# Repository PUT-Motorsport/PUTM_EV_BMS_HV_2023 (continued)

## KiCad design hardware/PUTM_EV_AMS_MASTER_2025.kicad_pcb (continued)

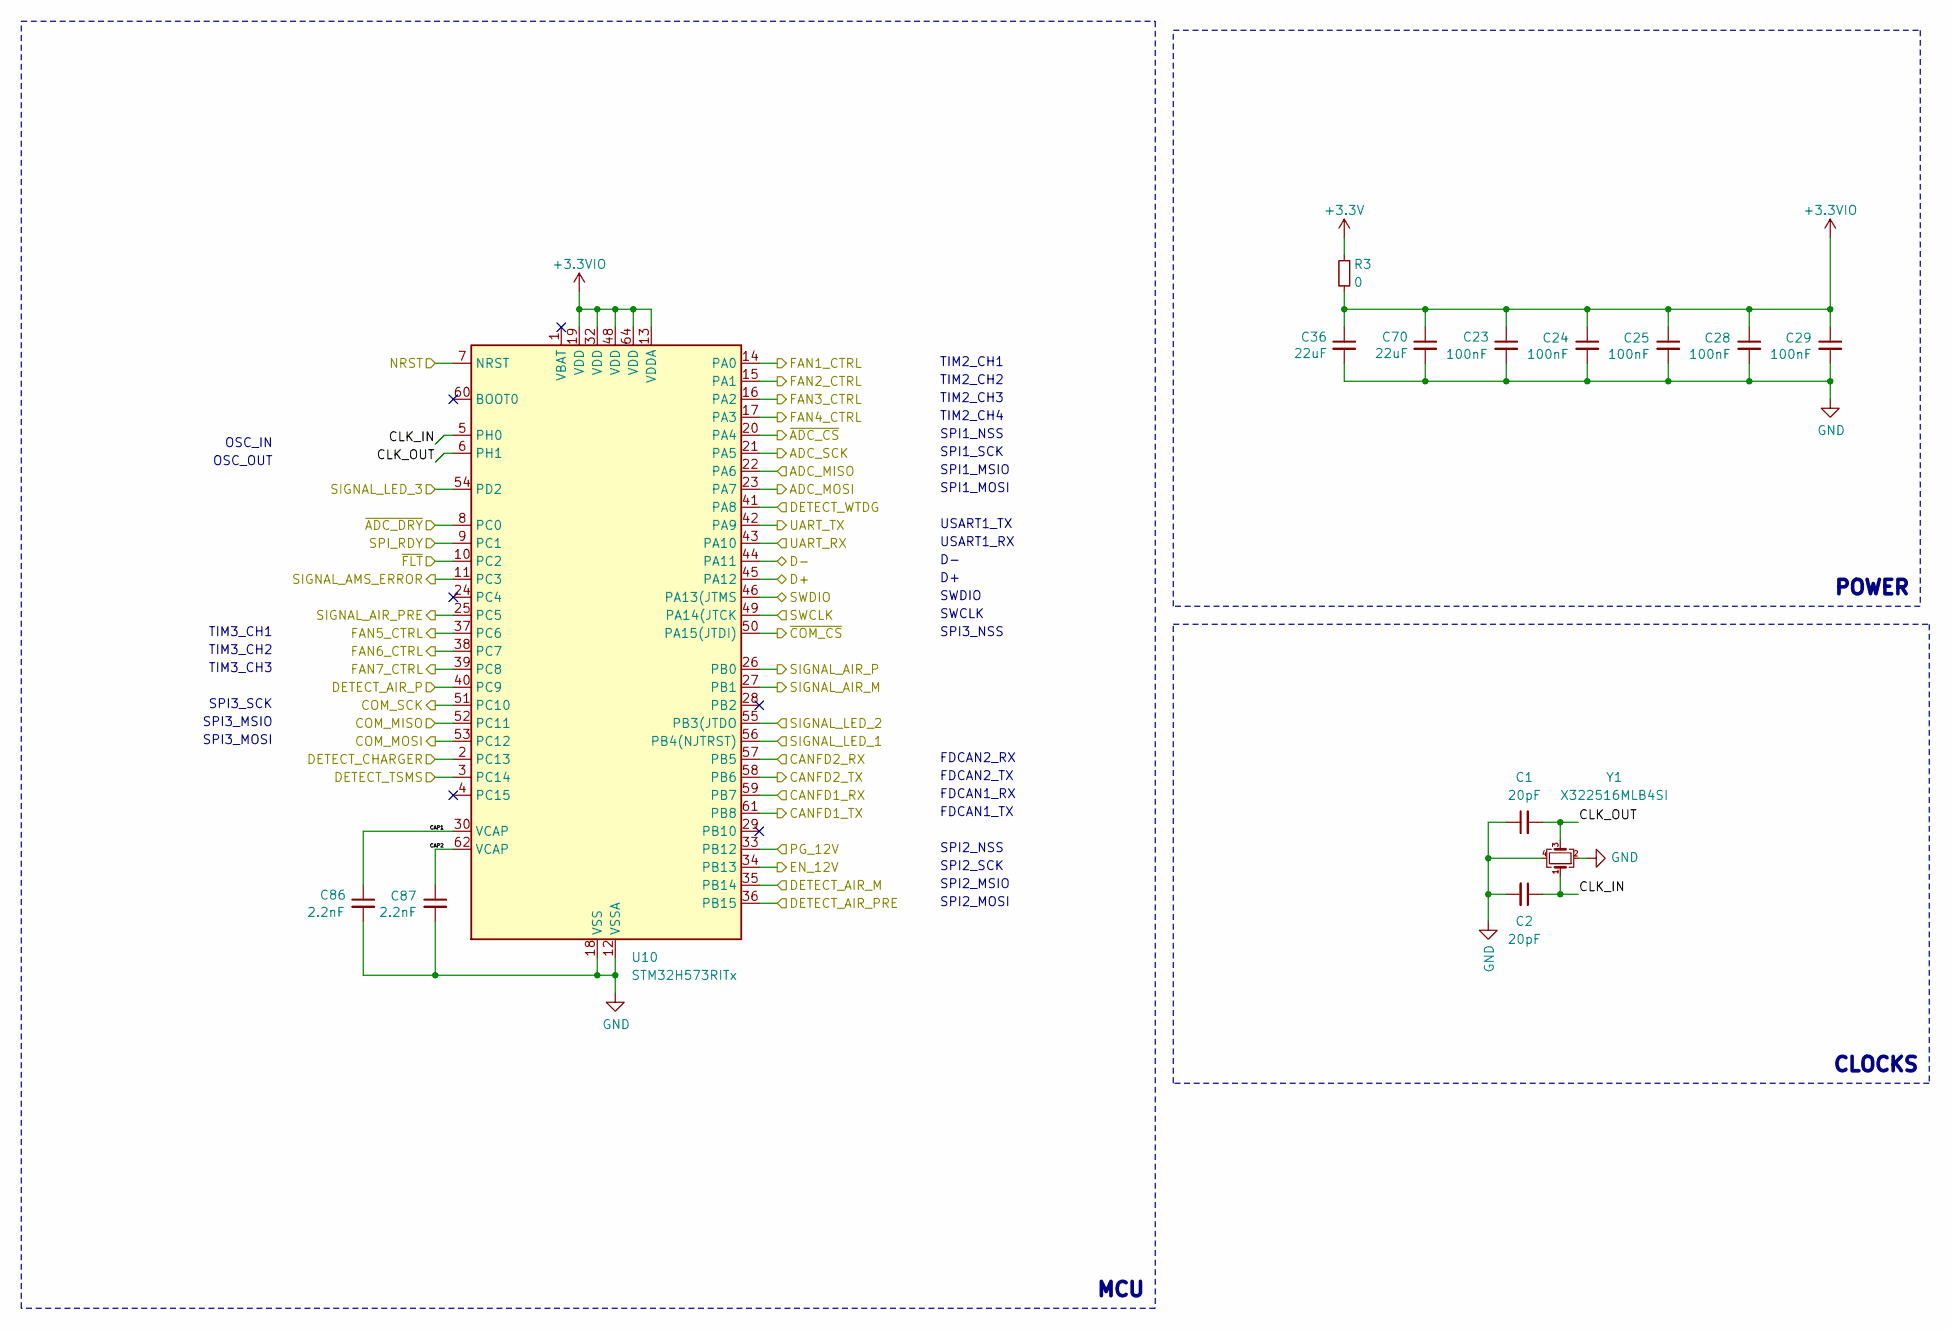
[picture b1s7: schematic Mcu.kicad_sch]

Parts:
C1, C2: 20pF; C_0603_1608Metric; Manufacturer_Part_Number --
C23, C24, C25, C28, C29: 100nF; C_0603_1608Metric; Manufacturer_Part_Number --
C36, C70: 22uF; C_0805_2012Metric; Manufacturer_Part_Number --
C86, C87: 2.2nF; C_0603_1608Metric; Manufacturer_Part_Number --
R3: 0; R_0603_1608Metric; Manufacturer_Part_Number --
U10: STM32H573RITx; LQFP-64_10x10mm_P0.5mm
Y1: X322516MLB4SI; Crystal_SMD_3225-4Pin_3.2x2.5mm; Manufacturer_Part_Number --

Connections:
+3.3V: R3.1; also elsewhere on the board
+3.3VIO: C23.1, C24.1, C25.1, C28.1, C29.1, C36.1, C70.1, R3.2, U10.13 (VDDA), U10.19 (VDD), U10.32 (VDD), U10.48 (VDD), U10.64 (VDD)
/AED: U10.36 (PB15); also elsewhere on the board
/AMD: U10.35 (PB14); also elsewhere on the board
/APD: U10.40 (PC9); also elsewhere on the board
/CD: U10.2 (PC13); also elsewhere on the board
/CRX1: U10.59 (PB7); also elsewhere on the board
/CRX2: U10.57 (PB5); also elsewhere on the board
/CTX1: U10.61 (PB8); also elsewhere on the board
/CTX2: U10.58 (PB6); also elsewhere on the board
/Connectivity/UC_D+: U10.45 (PA12); also elsewhere on the board
/Connectivity/UC_D-: U10.44 (PA11); also elsewhere on the board
/FC1: U10.14 (PA0); also elsewhere on the board
/FC2: U10.15 (PA1); also elsewhere on the board
/FC3: U10.16 (PA2); also elsewhere on the board
/FC4: U10.17 (PA3); also elsewhere on the board
/FC5: U10.37 (PC6); also elsewhere on the board
/FC6: U10.38 (PC7); also elsewhere on the board
/FC7: U10.39 (PC8); also elsewhere on the board
/MCU/ADC_MISO: U10.22 (PA6); also elsewhere on the board
/MCU/ADC_MOSI: U10.23 (PA7); also elsewhere on the board
/MCU/ADC_SCK: U10.21 (PA5); also elsewhere on the board
/MCU/CAP1: C86.1, U10.30 (VCAP)
/MCU/CAP2: C87.1, U10.62 (VCAP)
/MCU/CLK_IN: C2.1, U10.5 (PH0), Y1.1
/MCU/CLK_OUT: C1.2, U10.6 (PH1), Y1.3
/MCU/COM_MISO: U10.52 (PC11); also elsewhere on the board
/MCU/COM_MOSI: U10.53 (PC12); also elsewhere on the board
/MCU/COM_SCK: U10.51 (PC10); also elsewhere on the board
/MCU/DETECT_WTDG: U10.41 (PA8); also elsewhere on the board
/MCU/EN_12V: U10.34 (PB13); also elsewhere on the board
/MCU/PG_12V: U10.33 (PB12); also elsewhere on the board
/MCU/SIGNAL_AMS_ERROR: U10.11 (PC3); also elsewhere on the board
/MCU/SPI_RDY: U10.9 (PC1); also elsewhere on the board
/MCU/~ADC_CS: U10.20 (PA4); also elsewhere on the board
/MCU/~ADC_DRY: U10.8 (PC0); also elsewhere on the board
/MCU/~COM_CS: U10.50 (PA15(JTDI)); also elsewhere on the board
/MCU/~FLT: U10.10 (PC2); also elsewhere on the board
/NRST: U10.7 (NRST); also elsewhere on the board
/SAE: U10.25 (PC5); also elsewhere on the board
/SAM: U10.27 (PB1); also elsewhere on the board
/SAP: U10.26 (PB0); also elsewhere on the board
/SIGNAL_LED_1: U10.56 (PB4(NJTRST)); also elsewhere on the board
/SIGNAL_LED_2: U10.55 (PB3(JTDO); also elsewhere on the board
/SIGNAL_LED_3: U10.54 (PD2); also elsewhere on the board
/SWCLK: U10.49 (PA14(JTCK); also elsewhere on the board
/SWDIO: U10.46 (PA13(JTMS); also elsewhere on the board
/T: U10.3 (PC14); also elsewhere on the board
/UART_RX: U10.43 (PA10); also elsewhere on the board
/UART_TX: U10.42 (PA9); also elsewhere on the board
GND: C1.1, C2.2, C23.2, C24.2, C25.2, C28.2, C29.2, C36.2, C70.2, C86.2, C87.2, U10.12 (VSSA), U10.18 (VSS), U10.31 (VSS), U10.47 (VSS), U10.63 (VSS), Y1.2, Y1.4; also elsewhere on the board

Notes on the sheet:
MCU
USART1_RX
OSC_IN
USART1_TX
TIM2_CH4
FDCAN2_TX
SPI1_MSIO
TIM2_CH2
SPI3_MOSI
SPI2_SCK
OSC_OUT
FDCAN1_TX
SPI3_MSIO
SPI3_SCK
TIM3_CH2
SPI1_SCK
TIM2_CH3
CLOCKS
SPI3_NSS
SPI1_MOSI
TIM3_CH3
SPI1_NSS
SWDIO
SPI2_MOSI
SWCLK
FDCAN2_RX
SPI2_NSS
SPI2_MSIO
TIM2_CH1
TIM3_CH1
FDCAN1_RX
POWER

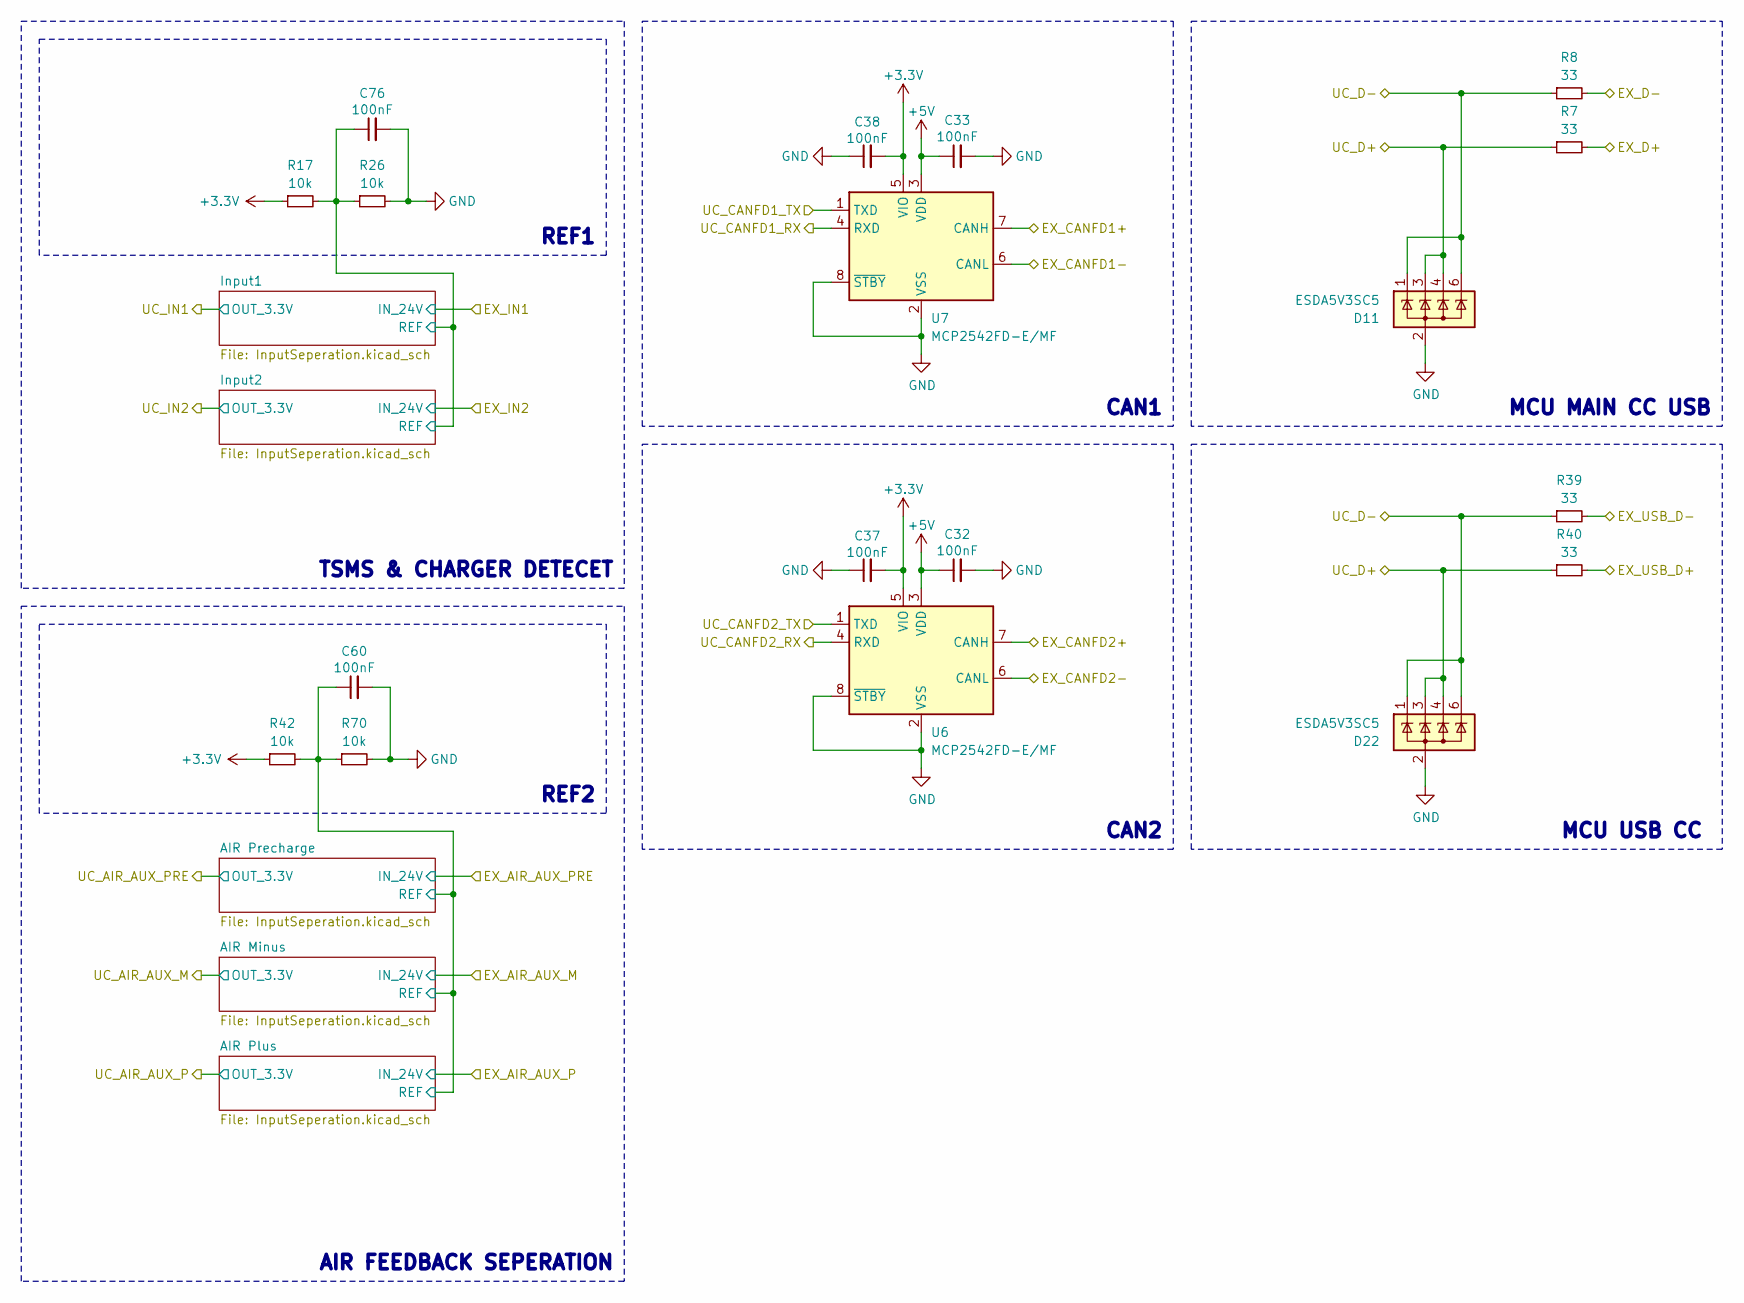
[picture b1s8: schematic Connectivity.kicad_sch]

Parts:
C32, C33, C37, C38, C60, C76: 100nF; C_0603_1608Metric; Manufacturer_Part_Number --
D11, D22: ESDA5V3SC5; SOT-23-6; Manufacturer_Part_Number ESDA5V3SC5; Mouser Part Number 511-ESDA5V3SC5
R7, R8, R39, R40: 33; R_0603_1608Metric; Manufacturer_Part_Number --
R17, R26, R42, R70: 10k; R_0603_1608Metric; Manufacturer_Part_Number --
U6, U7: MCP2542FD-E/MF; DFN-8-1EP_3x3mm_P0.65mm_EP1.55x2.4mm; Manufacturer_Part_Number MCP2542FD-E/MF; Mouser Part Number 579-MCP2542FD-E/MF

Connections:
+3.3V: C37.2, C38.2, R17.1, R42.1, U6.5 (VIO), U7.5 (VIO); also elsewhere on the board
+5V: C32.1, C33.1, U6.3 (VDD), U7.3 (VDD); also elsewhere on the board
/CANFD1+: U7.7 (CANH); also elsewhere on the board
/CANFD1-: U7.6 (CANL); also elsewhere on the board
/CANFD2+: U6.7 (CANH); also elsewhere on the board
/CANFD2-: U6.6 (CANL); also elsewhere on the board
/CC_D+: R7.2; also elsewhere on the board
/CC_D-: R8.2; also elsewhere on the board
/CRX1: U7.4 (RXD); also elsewhere on the board
/CRX2: U6.4 (RXD); also elsewhere on the board
/CTX1: U7.1 (TXD); also elsewhere on the board
/CTX2: U6.1 (TXD); also elsewhere on the board
/Connectivity/AIR Minus/REF: C60.1, R42.2, R70.1; also elsewhere on the board
/Connectivity/Input1/REF: C76.1, R17.2, R26.1; also elsewhere on the board
/Connectivity/UC_D+: D11.3 (A), D11.4 (A), D22.3 (A), D22.4 (A), R7.1, R40.1; also elsewhere on the board
/Connectivity/UC_D-: D11.1 (A), D11.6 (A), D22.1 (A), D22.6 (A), R8.1, R39.1; also elsewhere on the board
/USBR_D+: R40.2; also elsewhere on the board
/USBR_D-: R39.2; also elsewhere on the board
GND: C32.2, C33.2, C37.1, C38.1, C60.2, C76.2, D11.2 (K), D11.5 (NC), D22.2 (K), D22.5 (NC), R26.2, R70.2, U6.2 (VSS), U6.8 (~STBY), U6.9 (VSS), U7.2 (VSS), U7.8 (~STBY), U7.9 (VSS); also elsewhere on the board

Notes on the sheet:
MCU MAIN CC USB
TSMS & CHARGER DETECET
CAN1
REF2
AIR FEEDBACK SEPERATION
REF1
CAN2
MCU USB CC

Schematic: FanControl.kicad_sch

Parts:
D8, D13, D17, D18, D19, D20, D21: VSSB410S-E3/52T; D_SOD-123; Manufacturer_Part_Number VSSB410S-E3/52T; Mouser Part Number 625-VSSB410S-E3/52T
Q2, Q3, Q4, Q5: DMT6018LDR-7; DMT6018LDR7; Mouser Part Number 621-DMT6018LDR-7
R5, R30, R58, R59, R62, R63, R66: 100; R_0603_1608Metric; Manufacturer_Part_Number --
R56, R57, R60, R61, R64, R65, R67: 10k; R_0603_1608Metric; Manufacturer_Part_Number --

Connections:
+12V: D8.1 (K), D13.1 (K), D17.1 (K), D18.1 (K), D19.1 (K), D20.1 (K), D21.1 (K); also elsewhere on the board
/FAN1-: D8.2 (A), Q2.5 (D1); also elsewhere on the board
/FAN2-: D18.2 (A), Q2.6 (D2); also elsewhere on the board
/FAN3-: D13.2 (A), Q3.5 (D1); also elsewhere on the board
/FAN4-: D19.2 (A), Q3.6 (D2); also elsewhere on the board
/FAN5-: D17.2 (A), Q4.5 (D1); also elsewhere on the board
/FAN6-: D20.2 (A), Q4.6 (D2); also elsewhere on the board
/FAN7-: D21.2 (A), Q5.5 (D1); also elsewhere on the board
/FC1: R5.1; also elsewhere on the board
/FC2: R30.1; also elsewhere on the board
/FC3: R58.1; also elsewhere on the board
/FC4: R59.1; also elsewhere on the board
/FC5: R62.1; also elsewhere on the board
/FC6: R63.1; also elsewhere on the board
/FC7: R66.1; also elsewhere on the board
/Fan Control/G1: Q2.1 (G1), R5.2, R56.2
/Fan Control/G2: Q2.4 (G2), R30.2, R57.2
/Fan Control/G3: Q3.1 (G1), R58.2, R60.2
/Fan Control/G4: Q3.4 (G2), R59.2, R61.2
/Fan Control/G5: Q4.1 (G1), R62.2, R64.2
/Fan Control/G6: Q4.4 (G2), R63.2, R65.2
/Fan Control/G7: Q5.1 (G1), R66.2, R67.2
GND: Q2.2 (S1), Q2.3 (S2), Q3.2 (S1), Q3.3 (S2), Q4.2 (S1), Q4.3 (S2), Q5.2 (S1), R56.1, R57.1, R60.1, R61.1, R64.1, R65.1, R67.1; also elsewhere on the board

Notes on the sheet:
NMOS 2
NMOS 1
NMOS 4
UNUSED
NMOS 6
NMOS 3
NMOS 5
NMOS 7

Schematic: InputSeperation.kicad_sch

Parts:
C74: TBD; C_0603_1608Metric; Manufacturer_Part_Number --
C75: 100nF; C_0603_1608Metric; Manufacturer_Part_Number --
R82, R83: TBD; R_0603_1608Metric; Manufacturer_Part_Number --
U9: LM397; SOT-23-5; Manufacturer_Part_Number LM397MFX/NOPB; Mouser Part Number 926-LM397MFX/NOPB

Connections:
+24V: C75.1, U9.5 (VDD); also elsewhere on the board
/AIR_P_DETECTION: R83.2; also elsewhere on the board
/APD: U9.4; also elsewhere on the board
/Connectivity/AIR Minus/REF: U9.1; also elsewhere on the board
/Connectivity/AIR Plus/IN+: C74.1, R82.1, R83.1, U9.3
GND: C74.2, C75.2, R82.2, U9.2 (VSS); also elsewhere on the board

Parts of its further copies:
C5, C66, C72, C81: TBD; C_0603_1608Metric; Manufacturer_Part_Number --
C50, C71, C73, C82: 100nF; C_0603_1608Metric; Manufacturer_Part_Number --
R35, R38, R68, R69, R75, R76, R106, R107: TBD; R_0603_1608Metric; Manufacturer_Part_Number --
U2, U5, U8, U13: LM397; SOT-23-5; Manufacturer_Part_Number LM397MFX/NOPB; Mouser Part Number 926-LM397MFX/NOPB

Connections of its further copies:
+24V: C50.1, C71.1, C73.1, C82.1, U2.5 (VDD), U5.5 (VDD), U8.5 (VDD), U13.5 (VDD); also elsewhere on the board
/AED: U5.4; also elsewhere on the board
/AIR_M_DETECTION: R76.2; also elsewhere on the board
/AIR_PRE_DETECTION: R69.2; also elsewhere on the board
/AMD: U8.4; also elsewhere on the board
/CD: U2.4; also elsewhere on the board
/CHARGER_DETECTION: R38.2; also elsewhere on the board
/Connectivity/AIR Minus/IN+: C72.1, R75.1, R76.1, U8.3
/Connectivity/AIR Minus/REF: U5.1, U8.1; also elsewhere on the board
/Connectivity/AIR Precharge/IN+: C66.1, R68.1, R69.1, U5.3
/Connectivity/Input1/IN+: C81.1, R106.1, R107.1, U13.3
/Connectivity/Input1/REF: U2.1, U13.1; also elsewhere on the board
/Connectivity/Input2/IN+: C5.1, R35.1, R38.1, U2.3
/T: U13.4; also elsewhere on the board
GND: C5.2, C50.2, C66.2, C71.2, C72.2, C73.2, C81.2, C82.2, R35.2, R68.2, R75.2, R106.2, U2.2 (VSS), U5.2 (VSS), U8.2 (VSS), U13.2 (VSS); also elsewhere on the board
TSMS: R107.2; also elsewhere on the board

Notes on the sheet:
Used comparators instead of optocopulers - a bit cheaper, a bit more versetile and has a smaller footprint
1. Input stage with a possibility of choosing right settings 2. Reference point - it's set to 1.8V 3. Output - open drain need to set pull-up on mcu
[2]
[3]
INPUT SEPERATOR
[1]

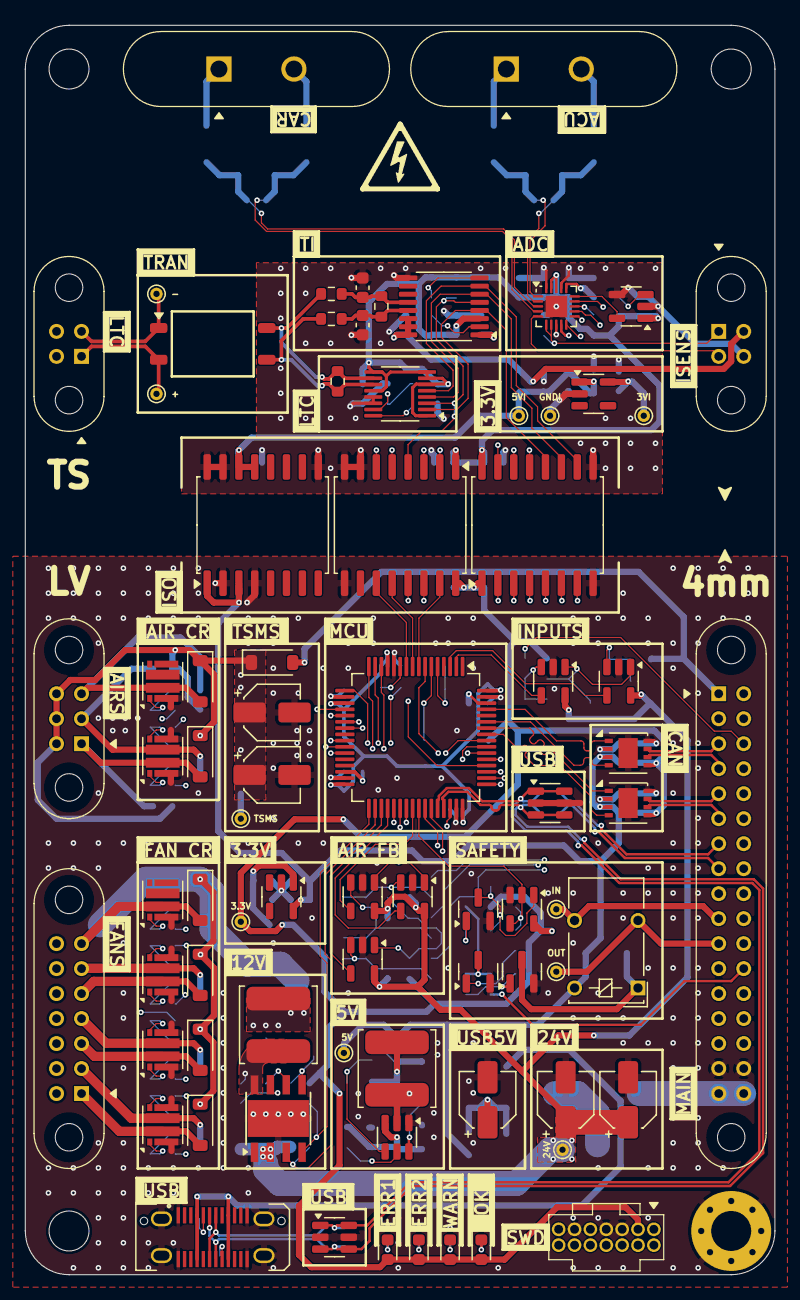
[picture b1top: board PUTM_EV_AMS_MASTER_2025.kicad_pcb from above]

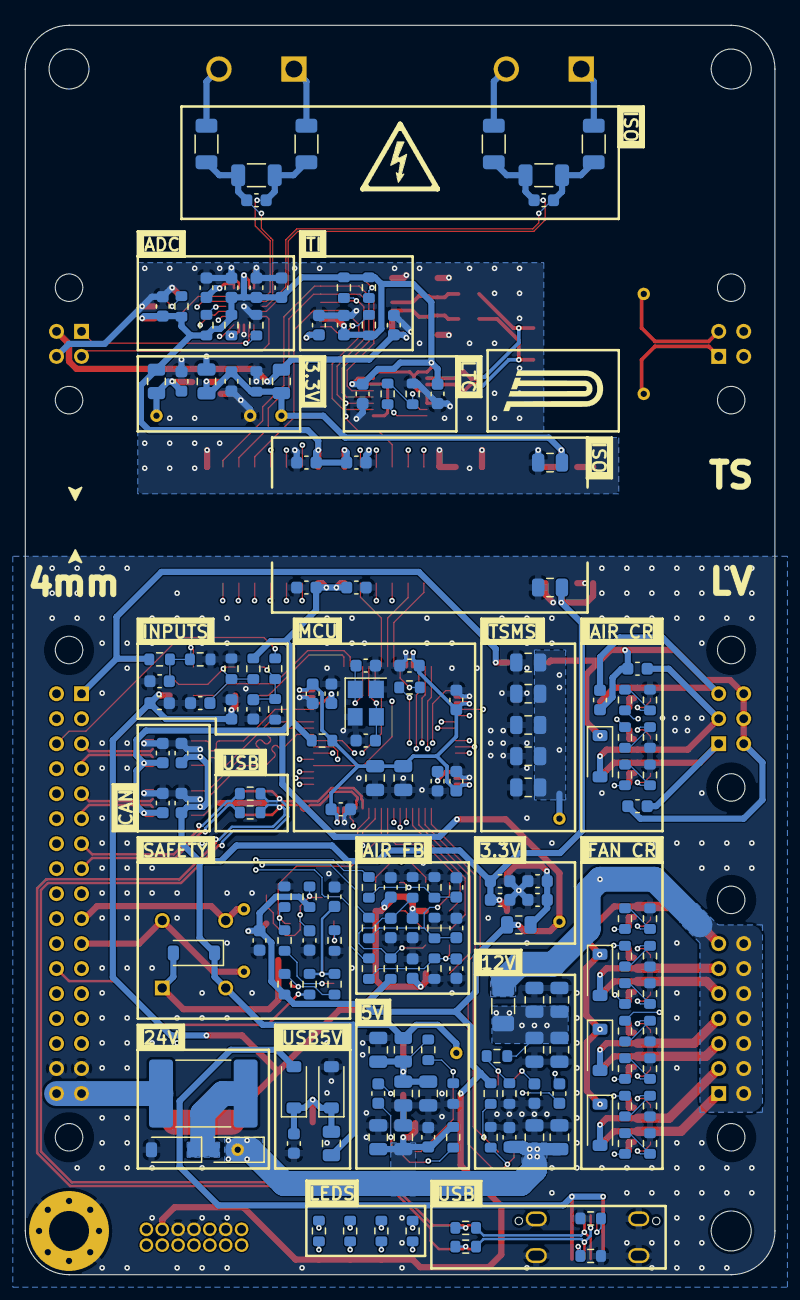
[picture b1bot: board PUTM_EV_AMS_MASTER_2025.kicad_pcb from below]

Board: 4 copper layers, 60.0 x 100.0 mm, 254 parts (173 on the bottom side), 164 nets.

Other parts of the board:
H1, H2, H3: M3; MountingHole_3.2mm_M3

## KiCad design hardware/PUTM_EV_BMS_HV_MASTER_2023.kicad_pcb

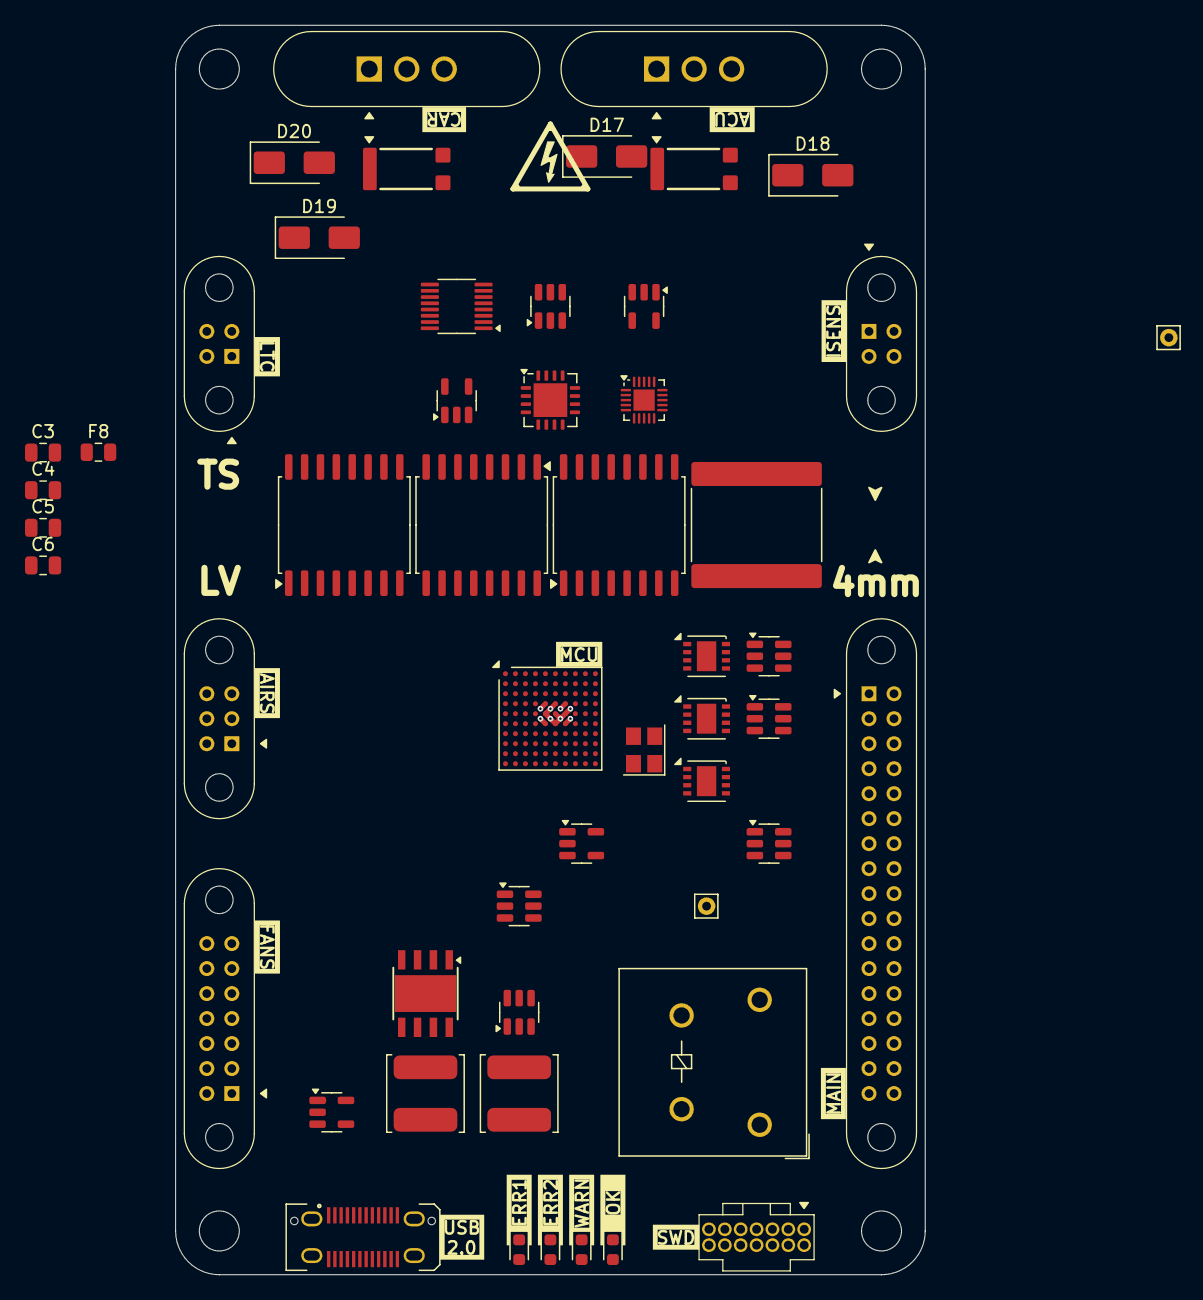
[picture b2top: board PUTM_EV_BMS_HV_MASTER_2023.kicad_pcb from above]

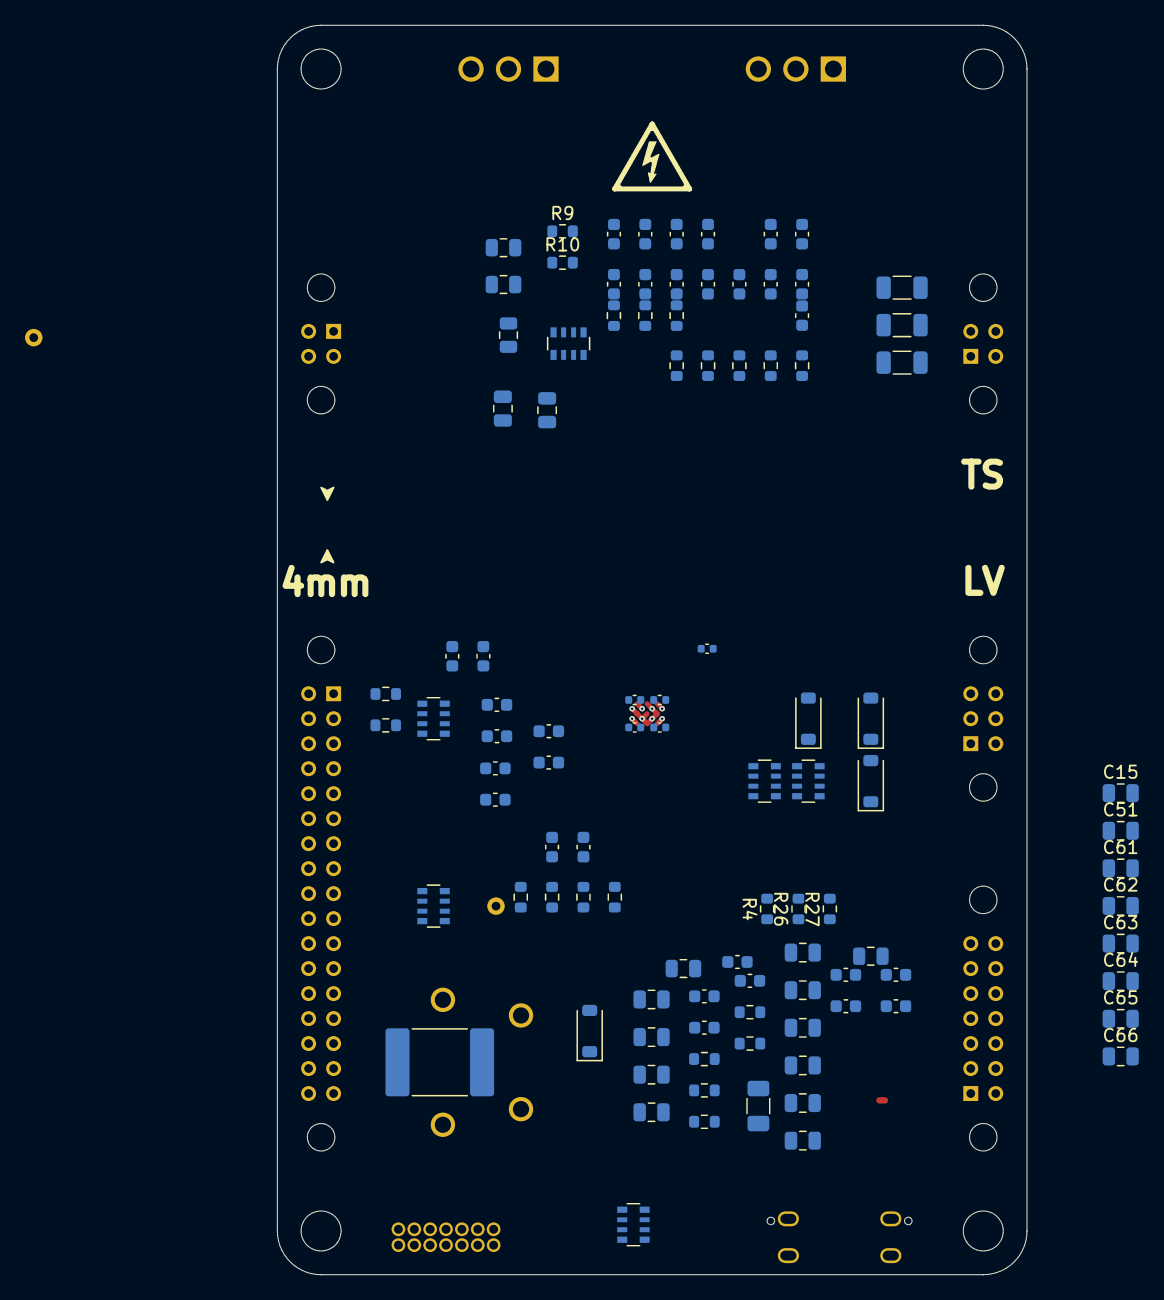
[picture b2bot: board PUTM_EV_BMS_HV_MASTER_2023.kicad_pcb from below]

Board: 4 copper layers, 60.0 x 100.0 mm, 157 parts (101 on the bottom side), 131 nets.

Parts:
C1, C2: 20pF; C_0603_1608Metric
C3, C4, C5, C6, C11, C12, C15, C16, C17, C19, C20, C26, C40, C51, C52, C54, C55, C59, C61, C62, C63, C64, C65, C66: 22uF; C_0805_2012Metric
C7, C8, C9, C10, C18, C21, C22, C27, C31, C32, C33, C35, C37, C38, C39, C42, C44, C45, C46, C47, C48, C49, C56, C57, C58, C60: 100nF; C_0603_1608Metric
C13, C14: 1uF; C_0603_1608Metric
C23, C24, C25, C28, C29: 100nF; C_0402_1005Metric
C34: 10nF; C_0603_1608Metric
C36, C43, C50: 10nF/1kV; C_1206_3216Metric
C41: 220nF; C_0603_1608Metric
C53: 5.6nF/2000V; C_3640_9110Metric
D1, D2, D3, D6: SML-D12U1WT86; LED_0603_1608Metric
D4, D5, D11, D12: ESDA5V3SC5; SOT-23-6
D7: SS16-LTP; D_SOD-123
D9, D10, D24: VSSB410S-E3/52T; D_SOD-123
D13: ESDA25SC6Y; SOT-23-6
D17, D18, D19, D20: 1.7V/1kV; D_SMA
F1, F4, F5, F6, F7, F8: 5V/0.5A; Fuse_0805_2012Metric
F2: 5A/24V; Fuse_2920_7451Metric
F3: 12V/4A; Fuse_1206_3216Metric
H1, H2, H3, H4: M3; MountingHole_3.2mm_M3
IC1, IC8: 3.3V/0.5A; SOT-23-5
IC2: TPS54202HDDCR; SOT-23-6
IC3: OPA1679-Q1; QFN-16-1EP_4x4mm_P0.65mm_EP2.7x2.7mm
IC4: ADS131M04; WQFN-20-1EP_3x3mm_P0.4mm_EP1.7x1.7mm
IC5: LTC1799; SOT-23-5
IC6: LTC6820IMS; MSOP-16_3x4.039mm_P0.5mm
IC7, IC11: ISO6760; SOIC-16W_7.5x10.3mm_P1.27mm
J1: M80-5100642; M80-51006YY
J2: USB_C_Receptacle_USB2.0_14P; USB_C_Receptacle_JAE_DX07S024WJ3R400
J3: M80-51014XX; M80-51014YY
J4: FTSH-107-01-L-D-K; FTSH-107-XX-YYY-D-K
J5, J8: M80-51004XX; M80-51004YY
J7, J10: M300-MV10345M1; M300MV10345M1
J12: M80-51034XX; M80-51034YY
K2: PB134024
L2: 6.8uF; L_TDK_VLS6045EX_VLS6045AF
L4: 68uF; L_TDK_VLS6045EX_VLS6045AF
R4, R10, R11, R13, R14, R17, R21, R26, R27: 10k; R_0603_1608Metric
R7, R8: 33; R_0603_1608Metric
R9, R15, R25, R28: 100k; R_0603_1608Metric
R12: 1M; R_0603_1608Metric
R16, R19: 1k; R_0603_1608Metric
R18: 8.2k; R_0603_1608Metric
R20: 120; R_0603_1608Metric
R22: 200; R_0603_1608Metric
R23: 510k; R_0603_1608Metric
R24: 9k; R_0603_1608Metric
R29: 13.3k; R_0603_1608Metric
RD1, RD2: 250:1; CDMA5M00F5000DE5
RN7: 4x1k; R_Array_Convex_4x0603
RN11, RN13: 100; R_Array_Convex_4x0603
RN12: 10k; R_Array_Convex_4x0603
RN16: 1k; R_Array_Convex_4x0603
RN17: 4x100; R_Array_Convex_4x0603
TP1, TP2: TestPoint_Small; Pin_D0.7mm_L6.5mm_W1.8mm_FlatFork
U1, U6, U7: MCP2542FD-E/MF; DFN-8-1EP_3x3mm_P0.65mm_EP1.55x2.4mm
U3: 74AUP1G32; SOT-23-5
U4: UCC12040DVE; SOIC-16W_7.5x10.3mm_P1.27mm
U10: STM32G484VEHx; TFBGA-100_8x8mm_Layout10x10_P0.8mm
U12: LMR33640DDDA; Texas_HSOP-8-1EP_3.9x4.9mm_P1.27mm
Y1: X322516MLB4SI; Crystal_SMD_3225-4Pin_3.2x2.5mm

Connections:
+3.3V: C8.2, C23.1, C24.1, C25.1, C28.1, C29.1, C37.2, C38.2, C39.1, C45.1, C58.2, D1.2 (A), D2.2 (A), D3.2 (A), D6.2 (A), F5.1, IC7.1 (VCC1), IC11.16 (VCC2), J4.3, R12.1, RN7.2 (R2.1), RN7.3 (R3.1), RN7.4 (R4.1), U1.5 (VIO), U3.5 (V), U6.5 (VIO), U7.5 (VIO), U10.D5 (VDD), U10.D7 (VDD), U10.F5 (VDD), U10.F7 (VDD), U10.J5 (VDDA), U10.K5 (VREF+)
+3.3VISO: C18.1, C27.1, C31.1, C34.1, C35.2, C42.1, C44.1, C46.1, C49.2, F6.1, IC3.3 (V+), IC4.18 (DVDD), IC4.19 (AVDD), IC5.1 (VDD), IC6.1 (EN), IC6.6 (VIO), IC6.7 (POL), IC6.8 (PHA), IC6.9 (VDD), IC6.12 (MSTR), IC7.16 (VCC2), IC11.1 (VCC1), R18.2, R21.2
+5V: C13.1, C32.1, C33.1, C56.2, C59.1, C60.1, F4.1, F8.1, IC1.5 (VO), U1.3 (VDD), U4.1 (EN), U4.3 (VINP), U6.3 (VDD), U7.3 (VDD)
+5VISO: F1.1, F7.1
+12V: F3.1, J3.8, J3.9, J3.10, J3.11, J3.12, J3.13, J3.14
+24V: C12.2, C17.2, C21.2, C52.2, C54.2, D7.1 (K), F2.1, IC2.3 (VIN), K2.A2 (COIL_2), R23.2, U12.2 (VIN), U12.3 (EN)
/AIR Control/SIGNAL1: RN11.8 (R1.2), U10.J7 (PE14)
/AIR Control/SIGNAL2: RN11.6 (R3.2), U10.K7 (PE13)
/AIR Control/SIGNAL3: RN11.7 (R2.2), U10.J6 (PE11)
/AIR_M: D9.2 (A), J1.1
/AIR_M_DETECTION: D13.3 (A), J12.13
/AIR_P: D10.2 (A), J1.2
/AIR_PRE: D24.2 (A), J1.3
/AIR_PRE_DETECTION: D13.1 (A), J12.12
/AIR_P_DETECTION: D13.4 (A), J12.14
/AMS_ERR: D6.1 (K), RN16.4 (R4.1)
/AMS_ERROR: R13.1, RN16.5 (R4.2)
/CANFD1+: J12.27, U7.7 (CANH)
/CANFD1-: J12.26, U7.6 (CANL)
/CANFD2+: J12.25, U6.7 (CANH)
/CANFD2-: J12.24, U6.6 (CANL)
/CANFD3+: J12.23, U1.7 (CANH)
/CANFD3-: J12.22, U1.6 (CANL)
/CHARGER_DETECTION: J12.10, R26.1
/Connectivity/AIR1_O: RN7.5 (R4.2), U10.A7 (PD5)
/Connectivity/AIR2_O: RN7.6 (R3.2), U10.A8 (PD4)
/Connectivity/AIR3_O: RN7.7 (R2.2), U10.A6 (PD6)
/Connectivity/CANFD1_RX: U7.4 (RXD), U10.B8 (PD0)
/Connectivity/CANFD1_TX: U7.1 (TXD), U10.A9 (PD1)
/Connectivity/CANFD2_RX: U6.4 (RXD), U10.B5
/Connectivity/CANFD2_TX: U6.1 (TXD), U10.A4 (PB6)
/Connectivity/CANFD3_RX: U1.4 (RXD), U10.A5 (PB3)
/Connectivity/CANFD3_TX: U1.1 (TXD), U10.C5 (PB4)
/Connectivity/D+_O: D11.4 (A), R7.1, U10.C9 (PA12)
/Connectivity/D-_O: D11.6 (A), R8.1, U10.C10 (PA11)
/D+: J2.A6 (D+), J2.B6 (D+), J12.17, R7.2
/D-: J2.A7 (D-), J2.B7 (D-), J12.16, R8.2
/F_+3VISO: C48.1, F6.2, IC8.5 (VO)
/F_+5VISO: C40.1, C47.2, F7.2, IC8.1 (VI), R22.2, U4.13 (SEL), U4.14 (VISO)
/IMD_SENSENSOR: J12.30, R27.1
/ISO_ADC_MISO: IC4.13 (SDO), IC11.3 (INB)
/ISO_ADC_MOSI: IC4.14 (SDI), IC7.15 (OUTA)
/ISO_ADC_SCK: IC4.12 (SCK), IC7.14 (OUTB)
/ISO_LTC_MISO: IC6.3 (MISO), IC11.4 (INC)
/ISO_LTC_MOSI: IC6.2 (MOSI), IC7.12 (OUTD)
/ISO_LTC_SCK: IC6.4 (SCK), IC7.11 (OUTE)
/Isolated ADC/8.192MHZ: IC4.15 (CLKIN), IC5.5 (OUT)
/Isolated ADC/ACU_V+: D17.1 (K), RD1.1
/Isolated ADC/ACU_V_ADC: IC3.1 (-), IC3.15, IC4.1 (CH0+)
/Isolated ADC/CAR_I: J8.1, RN13.6 (R3.2)
/Isolated ADC/CAR_I_ADC: IC3.7, IC3.8 (-), IC4.5 (CH2+)
/Isolated ADC/CAR_I_REF: J8.2, RN13.5 (R4.2)
/Isolated ADC/CAR_I_REF_ADC: IC3.12 (-), IC3.14, IC4.6 (CH2-), IC4.7 (CH3+)
/Isolated ADC/CAR_V+: D19.1 (K), RD2.1
/Isolated ADC/CAR_V_ADC: IC3.5 (-), IC3.6, IC4.3 (CH1+)
/Isolated SPI/I+: C50.1, IC6.10 (IM), R20.2
/Isolated SPI/I-: C43.1, IC6.11 (IP), R20.1
/LED1: D3.1 (K), RN16.3 (R3.1)
/LED2: D2.1 (K), RN16.2 (R2.1)
/LED3: D1.1 (K), RN16.1 (R1.1)
/MCU/ADC_MISO: IC11.14 (OUTB), U10.B1 (PE5)
/MCU/ADC_MOSI: IC7.2 (INA), U10.C2 (PE6)
/MCU/ADC_SCK: IC7.3 (INB), U10.C3 (PE2)
/MCU/CLK_IN: C2.1, U10.E1 (PF0), Y1.1
/MCU/CLK_OUT: C1.2, U10.E2 (PF1), Y1.3
/MCU/DETECT_WTDG: R14.2, U3.2, U3.4, U10.K10 (PD8)
/MCU/LTC_MISO: IC11.13 (OUTC), U10.H9 (PB14)
/MCU/LTC_MOSI: IC7.5 (IND), U10.K9 (PB15)
/MCU/LTC_SCK: IC7.6 (INE), U10.J9 (PB13)
/MCU/SIGNAL_AMS_ERROR: R11.1, U10.H7 (PE15)
/MCU/~ADC_CS: IC7.4 (INC), U10.A1 (PE4)
/MCU/~ADC_DRY: IC11.15 (OUTA), U10.B2 (PE3)
/MCU/~LTC_CS: IC7.7 (INF), U10.K8 (PB12)
/NRST: J4.12, U10.F3 (PG10)
/Power/F_+3.3V: C14.1, C57.2, F5.2, IC1.1 (VI)
/Power/F_+5V: C11.1, C26.1, F4.2, L4.2, R28.2
/Power/F_+12V: C16.1, C19.1, C20.1, C55.1, F3.2, L2.2, R25.2
/Power/SW_5V: C22.2, IC2.2 (SW), L4.1
/Power/SW_12V: C10.2, L2.1, U12.8 (SW)
/SAFETY1: J12.5, K2.14 (NO)
/SAFETY2: J12.6, K2.11 (COM)
/SHIELD: J5.3, J5.4
/SIGNAL_LED_1: RN16.6 (R3.2), U10.K6 (PE10)
/SIGNAL_LED_2: RN16.7 (R2.2), U10.H6 (PE9)
/SIGNAL_LED_3: RN16.8 (R1.2), U10.H5 (PE8)
/SWCLK: J4.6, U10.B10 (PA14)
/SWDIO: J4.4, U10.D8 (PA13)
/Safety/CAP_VOLT: C7.2, R12.2, U3.1
/Safety/RELAY-: D7.2 (A), K2.A1 (COIL_1)
/TSMS_AIRS: C15.2, C51.2, C61.2, C62.2, C63.2, C64.2, C65.2, C66.2, D9.1 (K), D10.1 (K), D24.1 (K), J1.4, J1.5, J1.6
/UART_RX: J4.13, U10.D9 (PA10)
/UART_TX: J4.14, U10.D10 (PA9)
/~ISO_ADC_CS: IC4.10 (~CS), IC7.13 (OUTC)
/~ISO_ADC_DRY: IC4.11 (~DRY), IC11.2 (INA)
/~ISO_LTC_CS: IC6.5 (~CS), IC7.10 (OUTF)
GND: C1.1, C2.2, C3.1, C4.1, C5.1, C6.1, C7.1, C8.1, C9.1, C11.2, C12.1, C13.2, C14.2, C15.1, C16.2, C17.1, C19.2, C20.2, C21.1, C23.2, C24.2, C25.2, C26.2, C28.2, C29.2, C32.2, C33.2, C37.1, C38.1, C39.2, C45.2, C51.1, C52.1, C53.1, C54.1, C55.2, C56.1, C57.1, C58.1, C59.2, C60.2, C61.1, C62.1, C63.1, C64.1, C65.1, C66.1, D5.2 (K), D5.5 (NC), D11.2 (K), D11.5 (NC), D12.2 (K), D12.5 (NC), D13.2 (K), D13.5 (NC), IC1.2 (GND), IC2.1 (GND), IC7.8 (GND1), IC11.9 (GND2), J2.A1 (GND), J2.A12 (GND), J2.B1 (GND), J2.B12 (GND), J2.S1 (SHIELD), J4.5, J4.7, J4.11, J12.3, J12.20, R11.2, R14.1, R24.1, R29.1, RN12.1 (R1.1), RN12.2 (R2.1), RN12.3 (R3.1), TP2.1, U1.2 (VSS), U1.8 (~STBY), U1.9 (VSS), U3.3 (G), U4.2 (GNDP), U4.4 (SYNC), U6.2 (VSS), U6.8 (~STBY), U6.9 (VSS), U7.2 (VSS), U7.8 (~STBY), U7.9 (VSS), U10.D2 (VSS), U10.D6 (VSS), U10.E5 (VSS), U10.E6 (VSS), U10.E7 (VSS), U10.F6 (VSS), U10.K4 (VSSA), U12.1 (GND), U12.9 (GND), Y1.2, Y1.4
GNDISO: C18.2, C27.2, C31.2, C34.2, C35.1, C36.1, C40.2, C41.1, C42.2, C44.2, C46.2, C47.1, C48.2, C49.1, C53.2, D4.2 (K), D4.5 (NC), D18.2 (A), D20.2 (A), IC3.10 (V-), IC3.17 (PAD), IC4.2 (CH0-), IC4.4 (CH1-), IC4.8 (CH3-), IC4.17 (DGND), IC4.20 (AGND), IC4.21 (PAD), IC5.2 (GND), IC5.4 (DIV), IC6.13 (SLOW), IC6.14 (GND), IC7.9 (GND2), IC8.2 (GND), IC11.5 (IND), IC11.6 (INE), IC11.7 (INF), IC11.8 (GND1), J8.4, R10.2, R17.2, R19.1, R22.1, RD1.2, RD2.2, TP1.1, U4.9 (GNDS), U4.15 (GNDS), U4.16 (GNDS)
I_VDDISO: F1.2, J8.3
unnamed: D5.1 (A), R27.2
unnamed: D5.3 (A), R26.2
unnamed: D5.4 (A), R4.2
unnamed: C4.2, C5.2, F8.2
unnamed: C22.1, IC2.6 (BOOT)
unnamed: IC2.5 (EN), R23.1
unnamed: IC2.4 (FB), R28.1, R29.2
unnamed: D4.6 (A), IC3.2 (+), RN13.1 (R1.1)
unnamed: D4.4 (A), IC3.4 (+), RN13.2 (R2.1)
unnamed: IC3.9 (+), R15.2, R17.1
unnamed: IC3.11 (+), R9.2, R10.1
unnamed: C41.2, IC4.16 (CAP)
unnamed: IC4.9 (~SYNC), R21.1
unnamed: IC5.3 (SET), R18.1
unnamed: IC6.16 (IBIAS), R16.2
unnamed: IC6.15 (ICMP), R16.1, R19.2
unnamed: RN11.1 (R1.1), RN12.8 (R1.2)
unnamed: RN11.2 (R2.1), RN12.7 (R2.2)
unnamed: RN11.3 (R3.1), RN12.6 (R3.2)
unnamed: RD1.3, RN13.8 (R1.2)
unnamed: RD2.3, RN13.7 (R2.2)
unnamed: D4.3 (A), R15.1, RN13.3 (R3.1)
unnamed: D4.1 (A), R9.1, RN13.4 (R4.1)
unnamed: D12.6 (A), RN17.8 (R1.2)
unnamed: D12.4 (A), RN17.7 (R2.2)
unnamed: D12.3 (A), RN17.6 (R3.2)
unnamed: D12.1 (A), RN17.5 (R4.2)
unnamed: C10.1, U12.7 (BOOT)
unnamed: R24.2, R25.1, U12.5 (FB)
unnamed: C9.2, U12.6 (VCC)
TSMS: J12.1, J12.18, R4.1
VBUS+: C3.2, C6.2, J2.A4 (VBUS), J2.A9 (VBUS), J2.B4 (VBUS), J2.B9 (VBUS)
VDD: F2.2, J12.2, J12.19
